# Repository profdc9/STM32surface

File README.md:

# STM32surface
This is a Bluepill-compatible devboard for the STM32F103C8T6 microcontroller.
It uses 0805 surface mount parts and a few through hole parts that can be easily obtained as
generic components.  It is intended to be an alternative should the 
should the Bluepill not be available, especially given the number of fake parts that have appeared lately.
The layout is somewhat optimized to be RFI resistant given it is a two-layer board
This material is copyrighted by Daniel Marks (KW4TI) and licensed under
the Creative Commons License CC-BY-SA 4.0.  Software is copyrighted using the zlib
open-source license.

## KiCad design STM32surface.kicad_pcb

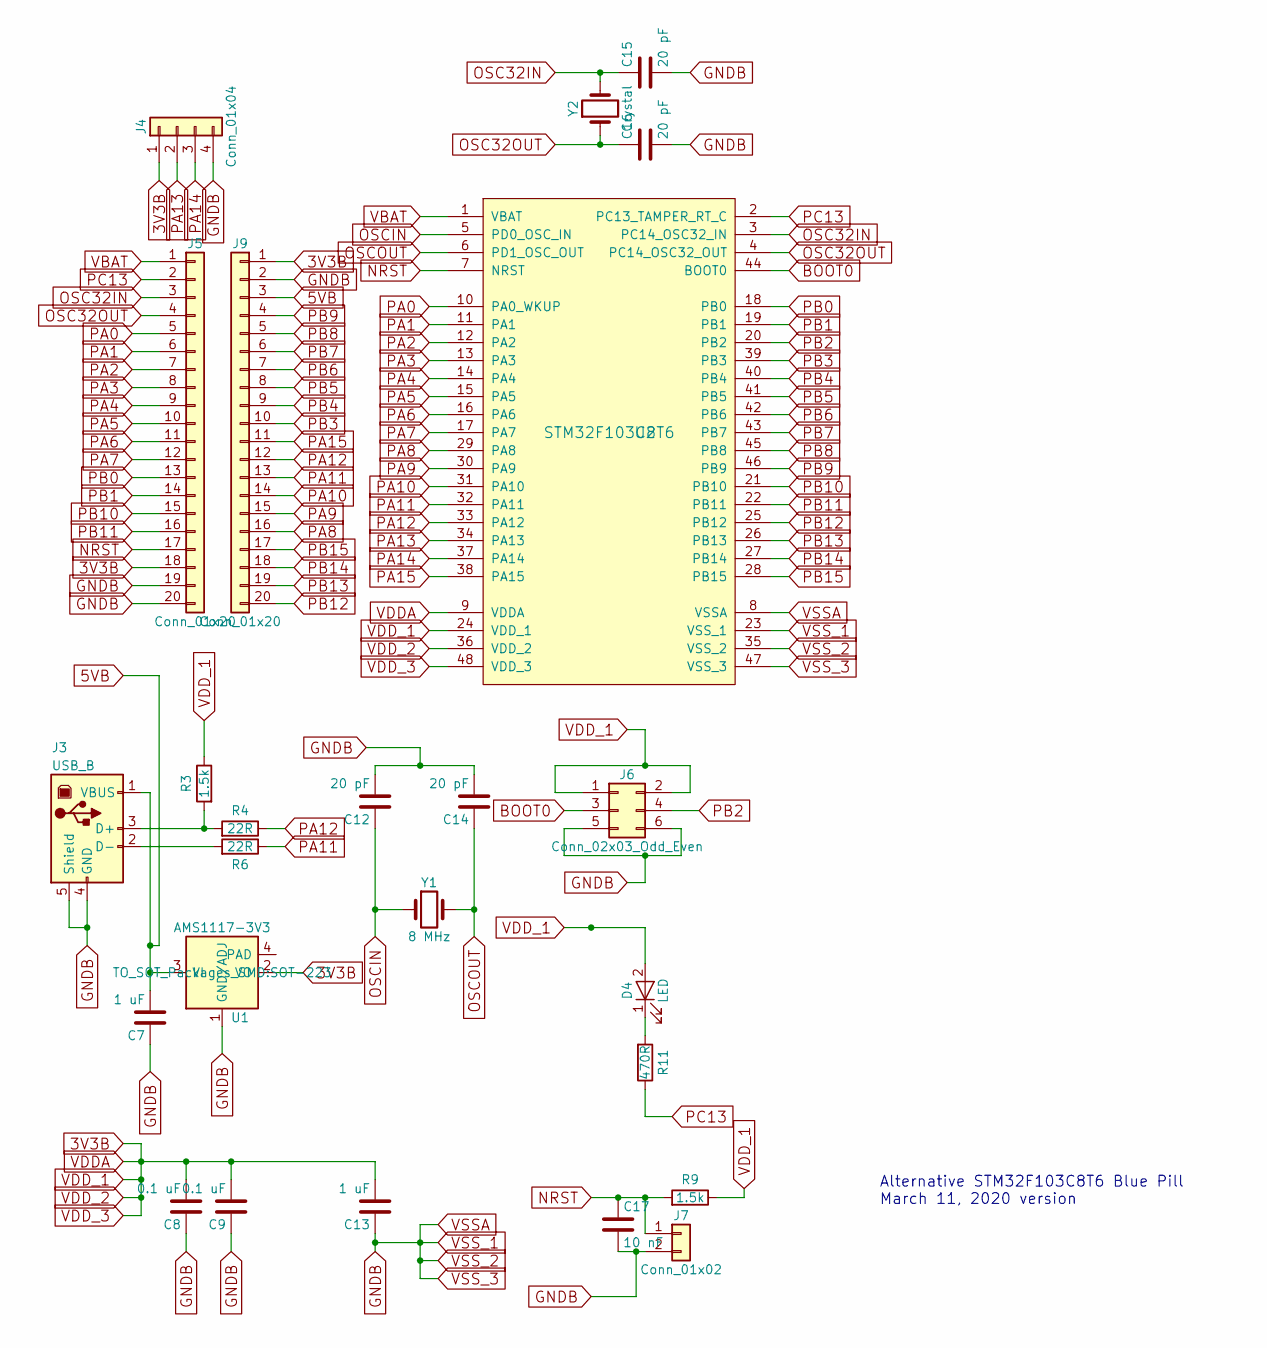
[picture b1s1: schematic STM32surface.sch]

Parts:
C7, C13: 1 uF; C_0805_HandSoldering; LCSC C28323
C8, C9: 0.1 uF; C_0805_HandSoldering; LCSC C49678
C12, C14, C15, C16: 20 pF; C_0805_HandSoldering; LCSC C1804
C17: 10 nF; C_0805_HandSoldering; LCSC C1710
D4: LED; LED_0805_HandSoldering; LCSC C2296
J3: USB_B
J4: Conn_01x04; Pin_Header_Straight_1x04_Pitch2.54mm
J5, J9: Conn_01x20; Pin_Header_Straight_1x20_Pitch2.54mm
J6: Conn_02x03_Odd_Even; Pin_Header_Straight_2x03_Pitch2.54mm
J7: Conn_01x02; SW_PUSH_6mm
R3, R9: 1.5k; R_0805_HandSoldering; LCSC C4310
R4, R6: 22R; R_0805_HandSoldering; LCSC C17561
R11: 470R; R_0805_HandSoldering; LCSC C17710
U1: AMS1117-3V3; SOT-223; MPN LM1117; LCSC C6186
U2: STM32F103C8T6; LQFP-48_7x7mm_Pitch0.5mm; LCSC C8304
Y1: 8 MHz; Crystal_SMD_5032-2pin_5.0x3.2mm; LCSC C115962
Y2: Crystal; Crystal_SMD_3215-2pin_3.2x1.5mm; LCSC C32346

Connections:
3V3B: C8.2, C9.2, C13.2, D4.2 (A), J4.1, J5.18, J6.1, J6.2, J9.1, R3.1, R9.1, U1.2 (VO), U2.9 (VDDA), U2.24 (VDD_1), U2.36 (VDD_2), U2.48 (VDD_3)
5VB: C7.2, J3.1 (VBUS), J9.3, U1.3 (VI)
BOOT0: J6.3, U2.44 (BOOT0)
GNDB: C7.1, C8.1, C9.1, C12.2, C13.1, C14.2, C15.2, C16.2, C17.2, J3.4 (GND), J3.5 (Shield), J4.4, J5.19, J5.20, J6.5, J6.6, J7.2, J9.2, U1.1 (GND/ADJ), U2.8 (VSSA), U2.23 (VSS_1), U2.35 (VSS_2), U2.47 (VSS_3)
NRST: C17.1, J5.17, J7.1, R9.2, U2.7 (NRST)
unnamed: D4.1 (K), R11.2
unnamed: J3.2 (D-), R6.2
unnamed: J3.3 (D+), R3.2, R4.2
OSC32IN: C15.1, J5.3, U2.3 (PC14_OSC32_IN), Y2.2
OSC32OUT: C16.1, J5.4, U2.4 (PC14_OSC32_OUT), Y2.1
OSCIN: C12.1, U2.5 (PD0_OSC_IN), Y1.1
OSCOUT: C14.1, U2.6 (PD1_OSC_OUT), Y1.2
PA0: J5.5, U2.10 (PA0_WKUP)
PA1: J5.6, U2.11 (PA1)
PA2: J5.7, U2.12 (PA2)
PA3: J5.8, U2.13 (PA3)
PA4: J5.9, U2.14 (PA4)
PA5: J5.10, U2.15 (PA5)
PA6: J5.11, U2.16 (PA6)
PA7: J5.12, U2.17 (PA7)
PA8: J9.16, U2.29 (PA8)
PA9: J9.15, U2.30 (PA9)
PA10: J9.14, U2.31 (PA10)
PA11: J9.13, R6.1, U2.32 (PA11)
PA12: J9.12, R4.1, U2.33 (PA12)
PA13: J4.2, U2.34 (PA13)
PA14: J4.3, U2.37 (PA14)
PA15: J9.11, U2.38 (PA15)
PB0: J5.13, U2.18 (PB0)
PB1: J5.14, U2.19 (PB1)
PB2: J6.4, U2.20 (PB2)
PB3: J9.10, U2.39 (PB3)
PB4: J9.9, U2.40 (PB4)
PB5: J9.8, U2.41 (PB5)
PB6: J9.7, U2.42 (PB6)
PB7: J9.6, U2.43 (PB7)
PB8: J9.5, U2.45 (PB8)
PB9: J9.4, U2.46 (PB9)
PB10: J5.15, U2.21 (PB10)
PB11: J5.16, U2.22 (PB11)
PB12: J9.20, U2.25 (PB12)
PB13: J9.19, U2.26 (PB13)
PB14: J9.18, U2.27 (PB14)
PB15: J9.17, U2.28 (PB15)
PC13: J5.2, R11.1, U2.2 (PC13_TAMPER_RT_C)
VBAT: J5.1, U2.1 (VBAT)

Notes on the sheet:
Alternative STM32F103C8T6 Blue Pill March 11, 2020 version

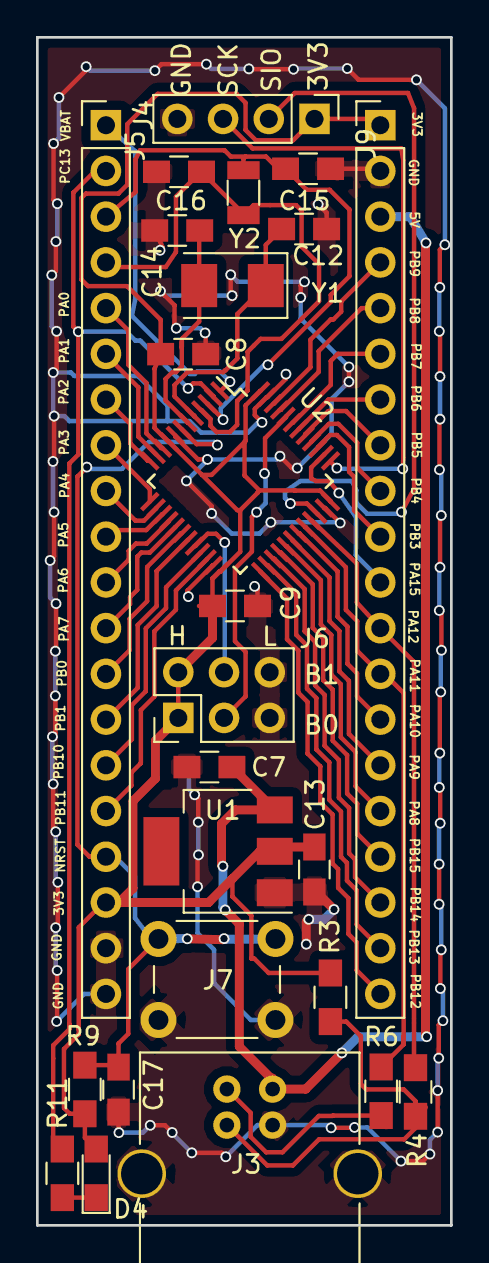
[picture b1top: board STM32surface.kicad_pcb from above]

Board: 2 copper layers, 23.0 x 66.0 mm, 25 parts (0 on the bottom side), 46 nets.

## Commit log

2020-06-23 Changed all to JLCPCB parts
2020-06-30 Added STM32surface-top.xlsx and STM32surface-BOM.xlsx
2020-10-11 Added STM32F3 BOM
